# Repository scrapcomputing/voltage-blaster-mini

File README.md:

# Voltage Blaster Mini

Voltage Blaster Mini is a smaller version of the Voltage Blaster by
Phil's Computer Lab and Necroware. It is a tiny ISA card that provides -5V.

For more information about the original Voltage Blaster please refer to <https://github.com/necroware/voltage-blaster>.

# How does it work ?

The input to the LM7905 voltage regulator are pins B1 (GND) and B7 (-12V).
The output is pin B5 (-5V).

The resistor and the LEDs are optional. They are only used to indicate that -5V
is being generated by the regulator.

# Bill of materials

Item                            | #   | Description
--------------------------------|-----|--------------------------------------------------------
LM7905                          | 1   | Negative 5 Volts Voltage Regulator
10 uF ceramic capacitors        | 2   |
1K 1/4 watt resistor            | 1   | (Optional) You can use smaller for a brighter LED
LED                             | 1   | (Optional) Indicator light that -5V is being generated

Gerber files can be found in the [releases](https://github.com/scrapcomputing/voltage-blaster-mini/releases).

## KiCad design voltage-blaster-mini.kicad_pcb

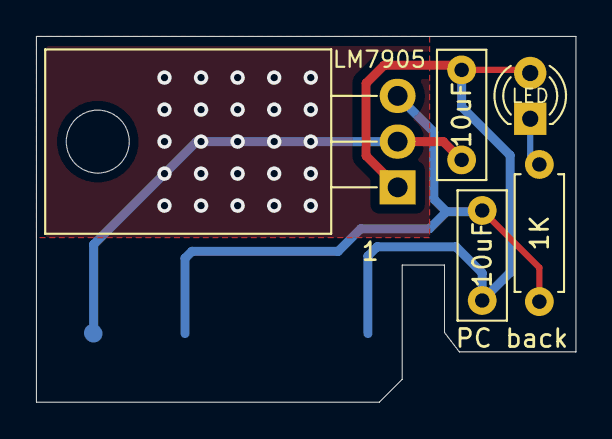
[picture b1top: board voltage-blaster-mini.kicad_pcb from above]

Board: 2 copper layers, 30.0 x 20.3 mm, 6 parts (0 on the bottom side), 4 nets.

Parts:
1K: 1K; R_Axial_DIN0207_L6.3mm_D2.5mm_P7.62mm_Horizontal
10uF, 10uF#2: 10uF; C_Rect_L7.0mm_W2.5mm_P5.00mm
J1: Bus_ISA_8bit; ISA_8BIT_EDGE
LED: -5V; LED_D3.0mm
LM7905: LM7905; TO-220-3_Horizontal_TabDown

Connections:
GND: 10uF.2, 10uF#2.1, J1.1, LED.2, LM7905.1
unnamed: 1K.1, 10uF#2.2, J1.5, LM7905.3
unnamed: 10uF.1, J1.7, LM7905.2
unnamed: 1K.2, LED.1

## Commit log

2023-01-07 Initial commit rev 0.1
2023-06-10 Adds link to gerber files.
